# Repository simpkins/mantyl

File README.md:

# Mantyl: concave split keyboard

This repository contains the CAD design code and firmware for my custom
keyboard.

# Keyboard Model

The `cad` directory contains code for generating the keyboard model, using
Python scripts for [Blender](https://www.blender.org/).

# Firmware

The `src` directory contains the firmware for the keyboard.  I use a
[FeatherS3](https://esp32s3.com/feathers3.html) for the microcontroller,
and the firmware code is built with the
[ESP-IDF](https://github.com/espressif/esp-idf).

# Gallery

Some more images can be found in the [img](img) directory.

# Documentation

The [doc](doc) directory contains various documentation.  The
[assembly.md](doc/assembly.md) and [wiring.md](doc/wiring.md) files may be of
interest if you are looking to print and assemble your own version of the
keyboard.

# Inspiration

I've used [Maltron](https://www.maltron.com/) keyboards for quite a long time.
My original Maltron keyboard was a PS/2 model, and back in 2013 I built my own
[keyboard controller](https://github.com/simpkins/avrpp) for it using a
[Teensy++ 2.0](https://www.pjrc.com/store/teensypp.html) microcontroller, in
order to convert it to a USB keyboard.

The layout for this keyboard is heavily influenced by the Maltron layout--I
wanted it to be fairly similar since I've used the Maltron layout for so long.

For generating the keyboard model programmatically I took some inspiration from
the [Dactyl-Manuform](https://github.com/abstracthat/dactyl-manuform) keyboard.
I initially started out using OpenSCAD, but quickly found it fairly limiting
and switched to using Python APIs for blender.  For some choices of the
electronic components, particularly the SX1509, I relied on some of the
component selection from my co-worker Wez's
[Halfdeck](https://github.com/wez/halfdeck) keyboard.

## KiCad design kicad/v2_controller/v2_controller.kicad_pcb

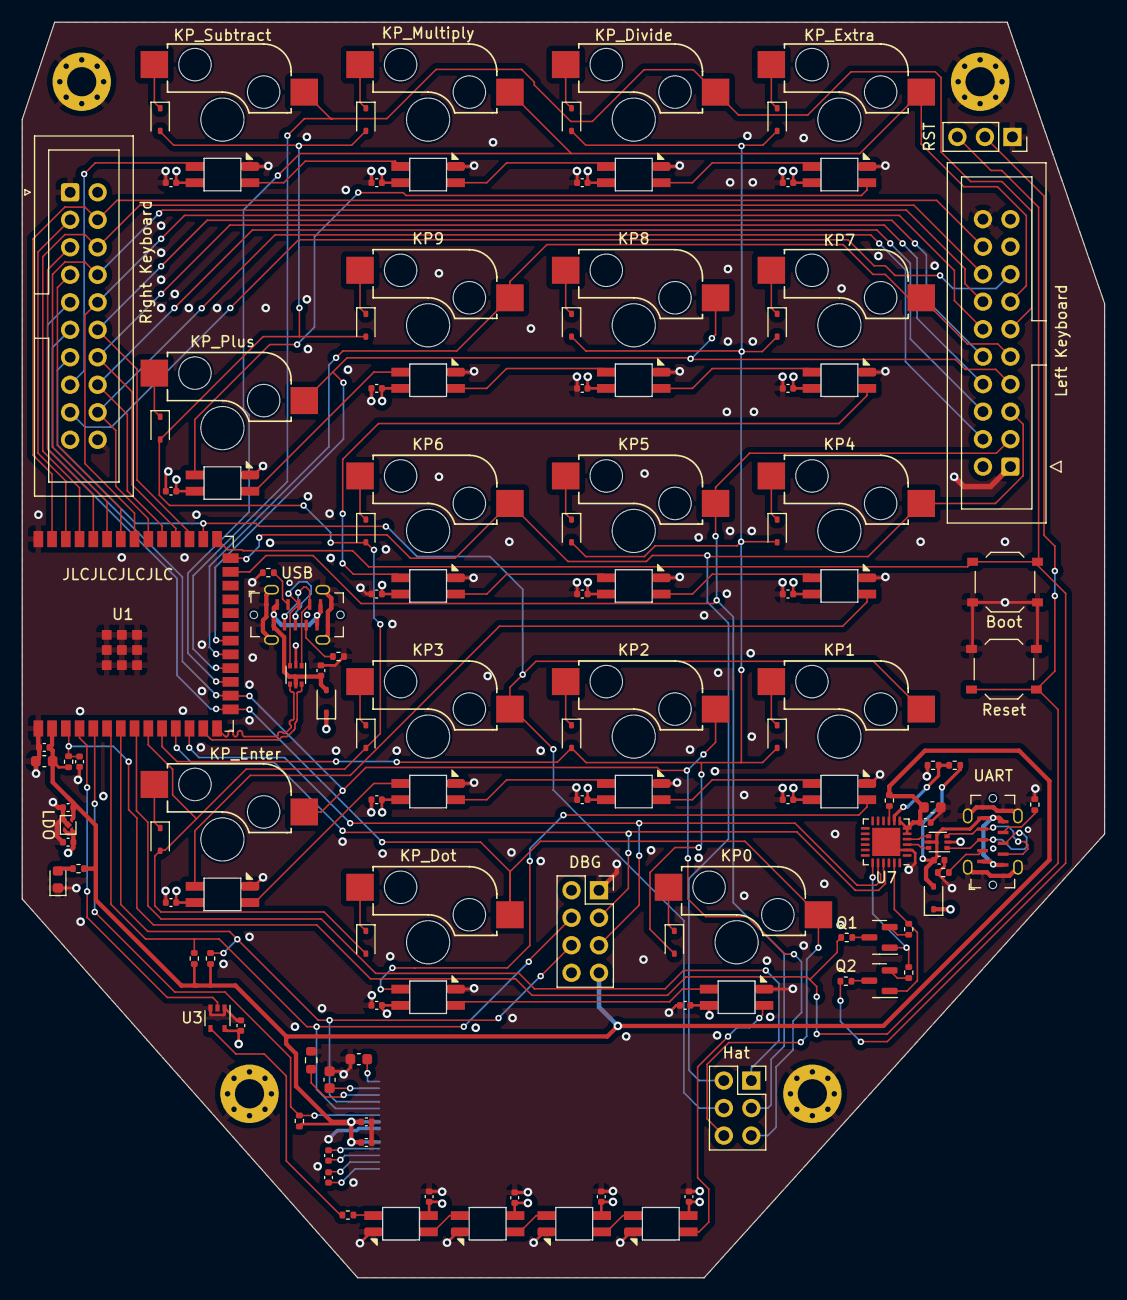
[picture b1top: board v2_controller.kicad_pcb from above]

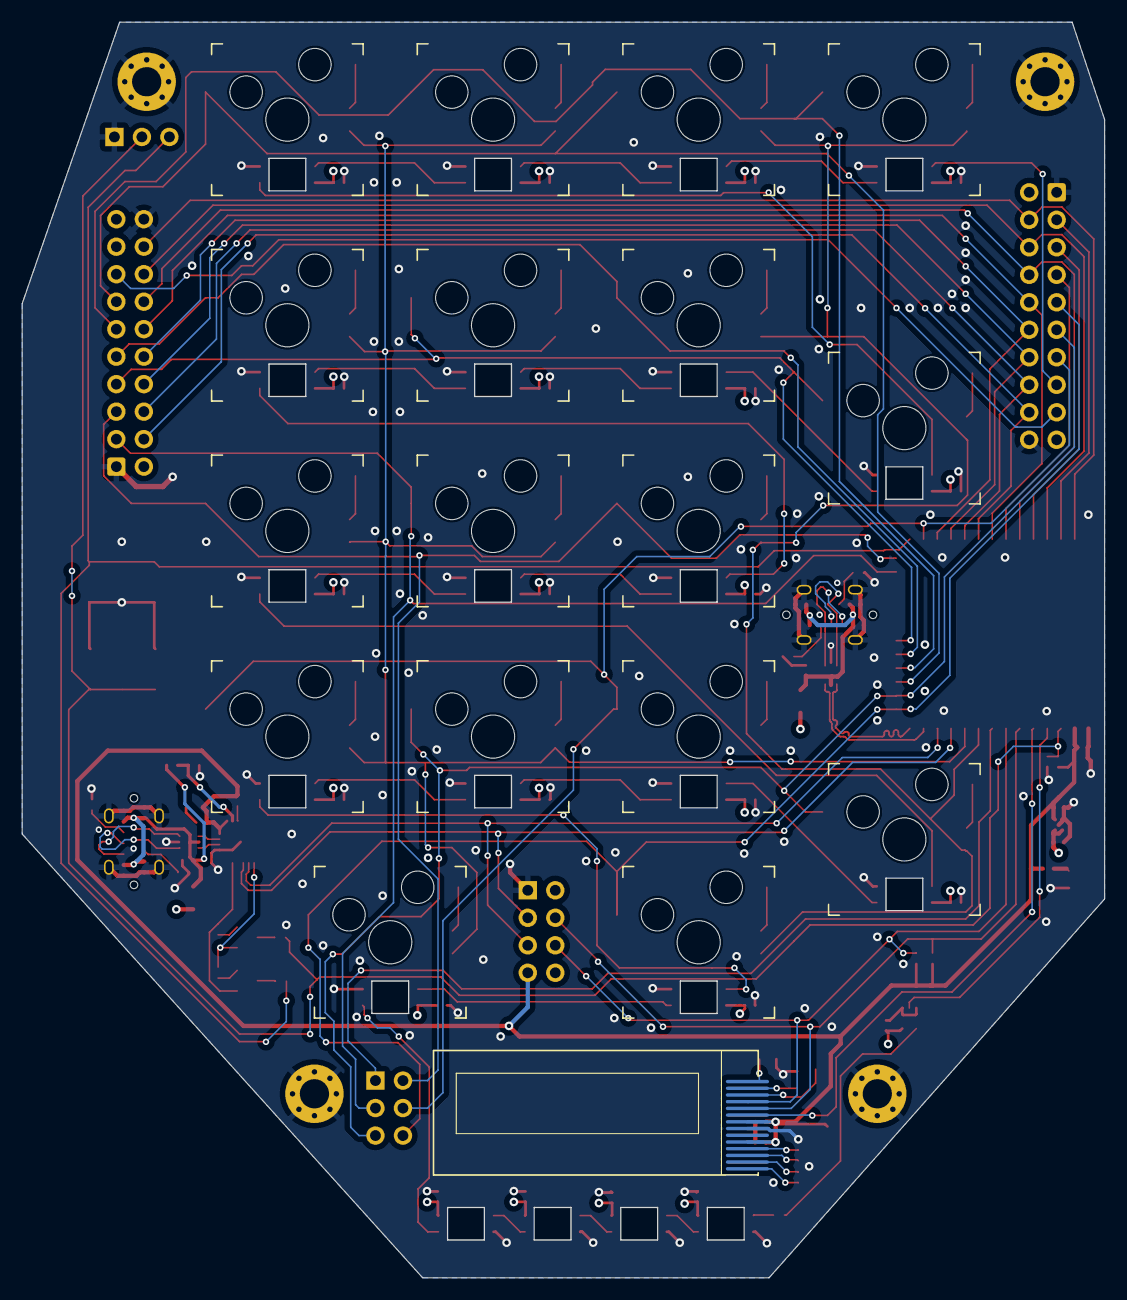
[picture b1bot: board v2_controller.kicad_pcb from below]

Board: 4 copper layers, 100.0 x 116.0 mm, 135 parts (18 on the bottom side), 105 nets.

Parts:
C1, C4, C5, C8, C9, C11, C12: 1uF; C_0402_1005Metric
C2, C6, C7, C17: 10uF; C_0603_1608Metric
C3, C10, C15, C16, C18, C19, C20, C21, C22, C23, C24, C25, C26, C27, C28, C29, C30, C31, C32, C33, C34, C35, C36, C37, C38, C39: 100nF; C_0402_1005Metric
D1, D2, D3, D4, D5, D6, D7, D8, D9, D10, D11, D12, D13, D14, D15, D16, D17, D38, D39, D40, D41: SK6812 Mini-E; SK6812-MINI-E
D18, D19: 1N5819WS; D_SOD-323
D20: Red LED; LED_0603_1608Metric
D21, D22, D23, D24, D25, D26, D27, D28, D29, D30, D31, D32, D33, D34, D35, D36, D37: 1N4148WS; D_SOD-323
H1, H2, H3, H4: MountingHole_Pad; MountingHole_2.7mm_M2.5_Pad_Via
J1, J2: USB_C_Receptacle_USB2.0; GT-USB-7090x
J3, J4: Conn_02x10_Odd_Even; IDC-Header_2x10_P2.54mm_Vertical
J5: Conn_02x04_Odd_Even; PinSocket_2x04_P2.54mm_Vertical
J6: Conn_02x03_Odd_Even; PinSocket_2x03_P2.54mm_Vertical
J7: Conn_01x03; PinSocket_1x03_P2.54mm_Vertical
Q1, Q2: S8050; SOT-23
R1, R4, R5, R17: 10k; R_0402_1005Metric
R2, R3: 4.7k; R_0402_1005Metric
R6, R7: 0; R_0402_1005Metric
R8, R9, R10, R11, R12: 5.1k; R_0402_1005Metric
R13: 22.1k; R_0402_1005Metric
R14: 47.5k; R_0402_1005Metric
R15: 1k; R_0402_1005Metric
R16: 470; R_0402_1005Metric
R18: 390k; R_0603_1608Metric
SW1: KP0; Kailh_socket_MX_platemount
SW2: KP_Dot; Kailh_socket_MX_platemount
SW3: KP1; Kailh_socket_MX_platemount
SW4: KP2; Kailh_socket_MX_platemount
SW5: KP3; Kailh_socket_MX_platemount
SW6: KP_Enter; Kailh_socket_MX_platemount
SW7: KP4; Kailh_socket_MX_platemount
SW8: KP5; Kailh_socket_MX_platemount
SW9: KP6; Kailh_socket_MX_platemount
SW10: KP7; Kailh_socket_MX_platemount
SW11: KP8; Kailh_socket_MX_platemount
SW12: KP9; Kailh_socket_MX_platemount
SW13: KP_Plus; Kailh_socket_MX_platemount
SW14: KP_Extra; Kailh_socket_MX_platemount
SW15: KP_Divide; Kailh_socket_MX_platemount
SW16: KP_Multiply; Kailh_socket_MX_platemount
SW17: KP_Subtract; Kailh_socket_MX_platemount
SW18: Boot; SW_Push_1P1T_XKB_TS-1187A
SW19: Reset; SW_Push_1P1T_XKB_TS-1187A
U1: ESP32-S3-WROOM-1-N16R8; ESP32-S3-WROOM-1
U2: SSD1306_I2C; SSD1306_OLED-0.91-128x32_Folded
U3: 74AHCT1G125; SOT-353_SC-70-5
U4: NCP167BMX330TBG; OnSemi_XDFN4-1EP_1.0x1.0mm_EP0.52x0.52mm
U5, U6: USBLC6-2P6; SOT-666
U7: CP2102N-Axx-xQFN24; QFN-24-1EP_4x4mm_P0.5mm_EP2.6x2.6mm

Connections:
+3.3V: C2.1, C3.1, C4.2, C5.2, C12.1, C17.2, C18.2, J5.7, R1.1, R2.1, R3.1, R12.2, R15.2, R17.1, U1.2 (3V3), U2.5 (VBAT), U2.8 (VDD), U4.1 (OUT), U7.5 (VIO), U7.6 (VDD), U7.7 (VREGIN)
+5V: C10.1, C11.1, C19.2, C20.2, C21.2, C22.2, C23.2, C24.2, C25.2, C26.2, C27.2, C28.2, C29.2, C30.2, C31.2, C32.2, C33.2, C34.2, C35.2, C36.2, C37.2, C38.2, C39.2, D1.1 (VDD), D2.1 (VDD), D3.1 (VDD), D4.1 (VDD), D5.1 (VDD), D6.1 (VDD), D7.1 (VDD), D8.1 (VDD), D9.1 (VDD), D10.1 (VDD), D11.1 (VDD), D12.1 (VDD), D13.1 (VDD), D14.1 (VDD), D15.1 (VDD), D16.1 (VDD), D17.1 (VDD), D18.1 (K), D19.1 (K), D38.1 (VDD), D39.1 (VDD), D40.1 (VDD), D41.1 (VDD), J3.2, J4.2, J5.2, U3.5 (VCC), U4.3 (EN), U4.4 (IN)
/ESP32/CHIP_PU: C1.1, J7.2, R1.2, R6.1, SW19.2, U1.3 (EN)
/ESP32/COL0: J3.18, J4.4, U1.39 (GPIO1)
/ESP32/COL1: J3.16, J4.6, U1.37 (GPIO43/U0TXD)
/ESP32/COL2: J3.14, J4.8, U1.35 (GPIO42)
/ESP32/COL3: J3.12, J4.10, U1.33 (GPIO40)
/ESP32/COL4: J3.10, J4.12, U1.29 (GPIO36)
/ESP32/COL5: J3.8, J4.14, U1.30 (GPIO37)
/ESP32/COL6: J3.6, J4.16, U1.31 (GPIO38)
/ESP32/COL7: J3.4, J4.18, U1.32 (GPIO39)
/ESP32/COL8: D21.2 (A), D23.2 (A), D24.2 (A), D27.2 (A), D28.2 (A), D30.2 (A), D31.2 (A), D34.2 (A), D35.2 (A), U1.10 (GPIO17/U1TXD)
/ESP32/COL9: D22.2 (A), D25.2 (A), D26.2 (A), D29.2 (A), D32.2 (A), D33.2 (A), D36.2 (A), D37.2 (A), U1.9 (GPIO16/XTAL_32K_N)
/ESP32/COL10: J6.1, U1.8 (GPIO15/XTAL_32K_P)
/ESP32/GPIO0: J7.3, R7.1, SW18.2, U1.27 (GPIO0/BOOT)
/ESP32/LED_DIN_3V3: U1.4 (GPIO4), U3.2
/ESP32/LED_LEFT_DIN: J3.15, J4.17
/ESP32/LED_NUMPAD_DIN: R16.1, U3.4
/ESP32/LED_RIGHT_DIN: D17.2 (DOUT), J4.15
/ESP32/OLED_RST: R17.2, U1.5 (GPIO5), U2.9 (RES#)
/ESP32/ROW0: J3.13, SW14.1, SW16.1, U1.17 (GPIO9)
/ESP32/ROW1: J3.11, SW15.1, SW17.1, U1.18 (GPIO10)
/ESP32/ROW2: J3.9, SW10.1, SW12.1, U1.19 (GPIO11)
/ESP32/ROW3: J3.7, SW11.1, SW13.1, U1.20 (GPIO12)
/ESP32/ROW4: J3.5, J6.2, SW7.1, SW9.1, U1.26 (GPIO45)
/ESP32/ROW5: J3.3, J6.3, SW8.1, U1.25 (GPIO48/SPICLK_N)
/ESP32/ROW6: J4.13, J6.4, SW3.1, SW5.1, U1.28 (GPIO35)
/ESP32/ROW7: J4.11, J6.5, SW4.1, SW6.1, U1.16 (GPIO46)
/ESP32/ROW8: J4.9, J6.6, SW1.1, SW2.1, U1.15 (GPIO3)
/ESP32/ROW9: J4.7, U1.34 (GPIO41)
/ESP32/ROW10: J4.5, U1.36 (GPIO44/U0RXD)
/ESP32/ROW11: J4.3, U1.38 (GPIO2)
/ESP32/SCL: J5.4, R2.2, U1.6 (GPIO6), U2.10 (SCL)
/ESP32/SDA: J5.6, R3.2, U1.7 (GPIO7), U2.11 (SDA)
/ESP32/UART_DTR: Q2.1 (E), R4.1, U7.23 (~DTR)
/ESP32/UART_RTS: Q1.1 (E), R5.1, U7.19 (~RTS)
/ESP32/UART_RX: J5.3, U1.11 (GPIO18/U1RXD), U7.21 (TXD)
/ESP32/UART_TX: J5.5, U1.12 (GPIO8), U7.20 (RXD)
/ESP32/USB_D+: U1.14 (GPIO20/USB_D+), U5.4 (I/O2)
/ESP32/USB_D-: U1.13 (GPIO19/USB_D-), U5.6 (I/O1)
/LEDs/LED_NP_MAIN_DIN: D1.4 (DIN), D41.2 (DOUT)
/USB/UART_USB_D+: U6.6 (I/O1), U7.3 (D+)
/USB/UART_USB_D-: U6.4 (I/O2), U7.4 (D-)
/USB/UART_USB_VBUS: C16.1, D19.2 (A), J2.A4 (VBUS), J2.A9 (VBUS), J2.B4 (VBUS), J2.B9 (VBUS), R13.1, U6.5 (VBUS)
/USB/USB_VBUS: C15.1, D18.2 (A), J1.A4 (VBUS), J1.A9 (VBUS), J1.B4 (VBUS), J1.B9 (VBUS), U5.5 (VBUS)
GND: C1.2, C2.2, C3.2, C4.1, C5.1, C6.2, C7.2, C10.2, C11.2, C12.2, C15.2, C16.2, C17.1, C18.1, C19.1, C20.1, C21.1, C22.1, C23.1, C24.1, C25.1, C26.1, C27.1, C28.1, C29.1, C30.1, C31.1, C32.1, C33.1, C34.1, C35.1, C36.1, C37.1, C38.1, C39.1, D1.3 (VSS), D2.3 (VSS), D3.3 (VSS), D4.3 (VSS), D5.3 (VSS), D6.3 (VSS), D7.3 (VSS), D8.3 (VSS), D9.3 (VSS), D10.3 (VSS), D11.3 (VSS), D12.3 (VSS), D13.3 (VSS), D14.3 (VSS), D15.3 (VSS), D16.3 (VSS), D17.3 (VSS), D20.1 (K), D38.3 (VSS), D39.3 (VSS), D40.3 (VSS), D41.3 (VSS), H1.1, H2.1, H3.1, H4.1, J1.A1 (GND), J1.A12 (GND), J1.B1 (GND), J1.B12 (GND), J1.S1 (SHIELD), J2.A1 (GND), J2.A12 (GND), J2.B1 (GND), J2.B12 (GND), J2.S1 (SHIELD), J3.1, J3.20, J4.1, J4.20, J5.1, J7.1, R8.2, R9.2, R10.2, R11.2, R14.2, R18.2, SW18.1, SW19.1, U1.1 (GND), U1.40 (GND), U1.41 (GND), U2.7 (VSS), U3.1, U3.3 (GND), U4.2 (GND), U4.5 (EPAD), U5.2 (GND), U6.2 (GND), U7.2 (GND), U7.25 (GND)
unnamed: D1.2 (DOUT), D2.4 (DIN)
unnamed: D2.2 (DOUT), D3.4 (DIN)
unnamed: D3.2 (DOUT), D4.4 (DIN)
unnamed: D4.2 (DOUT), D5.4 (DIN)
unnamed: D5.2 (DOUT), D6.4 (DIN)
unnamed: D6.2 (DOUT), D7.4 (DIN)
unnamed: D7.2 (DOUT), D8.4 (DIN)
unnamed: D8.2 (DOUT), D9.4 (DIN)
unnamed: D9.2 (DOUT), D10.4 (DIN)
unnamed: D10.2 (DOUT), D11.4 (DIN)
unnamed: D11.2 (DOUT), D12.4 (DIN)
unnamed: D12.2 (DOUT), D13.4 (DIN)
unnamed: D13.2 (DOUT), D14.4 (DIN)
unnamed: D14.2 (DOUT), D15.4 (DIN)
unnamed: D15.2 (DOUT), D16.4 (DIN)
unnamed: D16.2 (DOUT), D17.4 (DIN)
unnamed: D20.2 (A), R12.1
unnamed: D21.1 (K), SW1.2
unnamed: D22.1 (K), SW2.2
unnamed: D23.1 (K), SW3.2
unnamed: D24.1 (K), SW4.2
unnamed: D25.1 (K), SW5.2
unnamed: D26.1 (K), SW6.2
unnamed: D27.1 (K), SW7.2
unnamed: D28.1 (K), SW8.2
unnamed: D29.1 (K), SW9.2
unnamed: D30.1 (K), SW10.2
unnamed: D31.1 (K), SW11.2
unnamed: D32.1 (K), SW12.2
unnamed: D33.1 (K), SW13.2
unnamed: D34.1 (K), SW14.2
unnamed: D35.1 (K), SW15.2
unnamed: D36.1 (K), SW16.2
unnamed: D37.1 (K), SW17.2
unnamed: D38.4 (DIN), R16.2
unnamed: D38.2 (DOUT), D39.4 (DIN)
unnamed: D39.2 (DOUT), D40.4 (DIN)
unnamed: D40.2 (DOUT), D41.4 (DIN)
unnamed: J1.A5 (CC1), R8.1
unnamed: J1.B5 (CC2), R9.1
unnamed: J1.A6 (D+), J1.B6 (D+), U5.3 (I/O2)
unnamed: J1.A7 (D-), J1.B7 (D-), U5.1 (I/O1)
unnamed: J2.A5 (CC1), R10.1
unnamed: J2.B5 (CC2), R11.1
unnamed: J2.A6 (D+), J2.B6 (D+), U6.1 (I/O1)
unnamed: J2.A7 (D-), J2.B7 (D-), U6.3 (I/O2)
unnamed: Q1.2 (B), R4.2
unnamed: Q1.3 (C), R6.2
unnamed: Q2.2 (B), R5.2
unnamed: Q2.3 (C), R7.2
unnamed: C8.1, U2.4 (C1N)
unnamed: C8.2, U2.3 (C1P)
unnamed: C9.1, U2.2 (C2N)
unnamed: C9.2, U2.1 (C2P)
unnamed: R18.1, U2.12 (IREF)
unnamed: C6.1, U2.14 (VCC)
unnamed: C7.1, U2.13 (VCOMH)
unnamed: R13.2, R14.1, U7.8 (VBUS)
unnamed: R15.1, U7.9 (~RST)

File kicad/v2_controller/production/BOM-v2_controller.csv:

"Comment","Designator","Footprint","LCSC"
"1k","R15","R0402","C11702"
"74AHCT1G125","U3","SOT-353_SC-70-5","C151417"
"0","R6,R7","R0402","C17168"
"1N5819WS","D18,D19","SOD-323","C191023"
"1N4148WS","D21,D22,D23,D24,D25,D26,D27,D28,D29,D30,D31,D32,D33,D34,D35,D36,D37","SOD-323","C2128"
"S8050","Q1,Q2","SOT-23","C2150"
"Red LED","D20","LED0603","C2286"
"390k","R18","R0603","C23150"
"470","R16","R0402","C25117"
"10k","R1,R17,R4,R5","R0402","C25744"
"22.1k","R13","R0402","C25768"
"47.5k","R14","R0402","C25792"
"4.7k","R2,R3","R0402","C25900"
"5.1k","R10,R11,R12,R8,R9","R0402","C25905"
"USBLC6-2P6","U5,U6","SOT-666","C2827693"
"Conn_02x03_Odd_Even","J6","PinSocket_2x03_P2.54mm_Vertical","C2829893"
"ESP32-S3-WROOM-1-N16R8","U1","ESP32-S3-WROOM-1","C2913202"
"USB_C_Receptacle_USB2.0","J1,J2","GT-USB-7090x","C3019715"
"100nF","C10,C15,C16,C18,C19,C20,C21,C22,C23,C24,C25,C26,C27,C28,C29,C3,C30,C31,C32,C33,C34,C35,C36,C37,C38,C39","C0402","C307331"
"Boot","SW18,SW19","SW_Push_1P1T_XKB_TS-1187A","C318884"
"Conn_02x10_Odd_Even","J3,J4","IDC-Header_2x10_P2.54mm_Vertical","C3405"
"SK6812 Mini-E","D1,D10,D11,D12,D13,D14,D15,D16,D17,D2,D3,D38,D39,D4,D40,D41,D5,D6,D7,D8,D9","SK6812-MINI-E","C5149201"
"KP0","SW1,SW10,SW11,SW12,SW13,SW14,SW15,SW16,SW17,SW2,SW3,SW4,SW5,SW6,SW7,SW8,SW9","Kailh_socket_MX_platemount","C5156480"
"1uF","C1,C11,C12,C4,C5,C8,C9","C0402","C52923"
"NCP167BMX330TBG","U4","OnSemi_XDFN4-1EP_1.0x1.0mm_EP0.52x0.52mm","C892227"
"10uF","C17,C2,C6,C7","C0603","C96446"
"CP2102N-Axx-xQFN24","U7","QFN-24-1EP_4x4mm_P0.5mm_EP2.6x2.6mm","C969151"

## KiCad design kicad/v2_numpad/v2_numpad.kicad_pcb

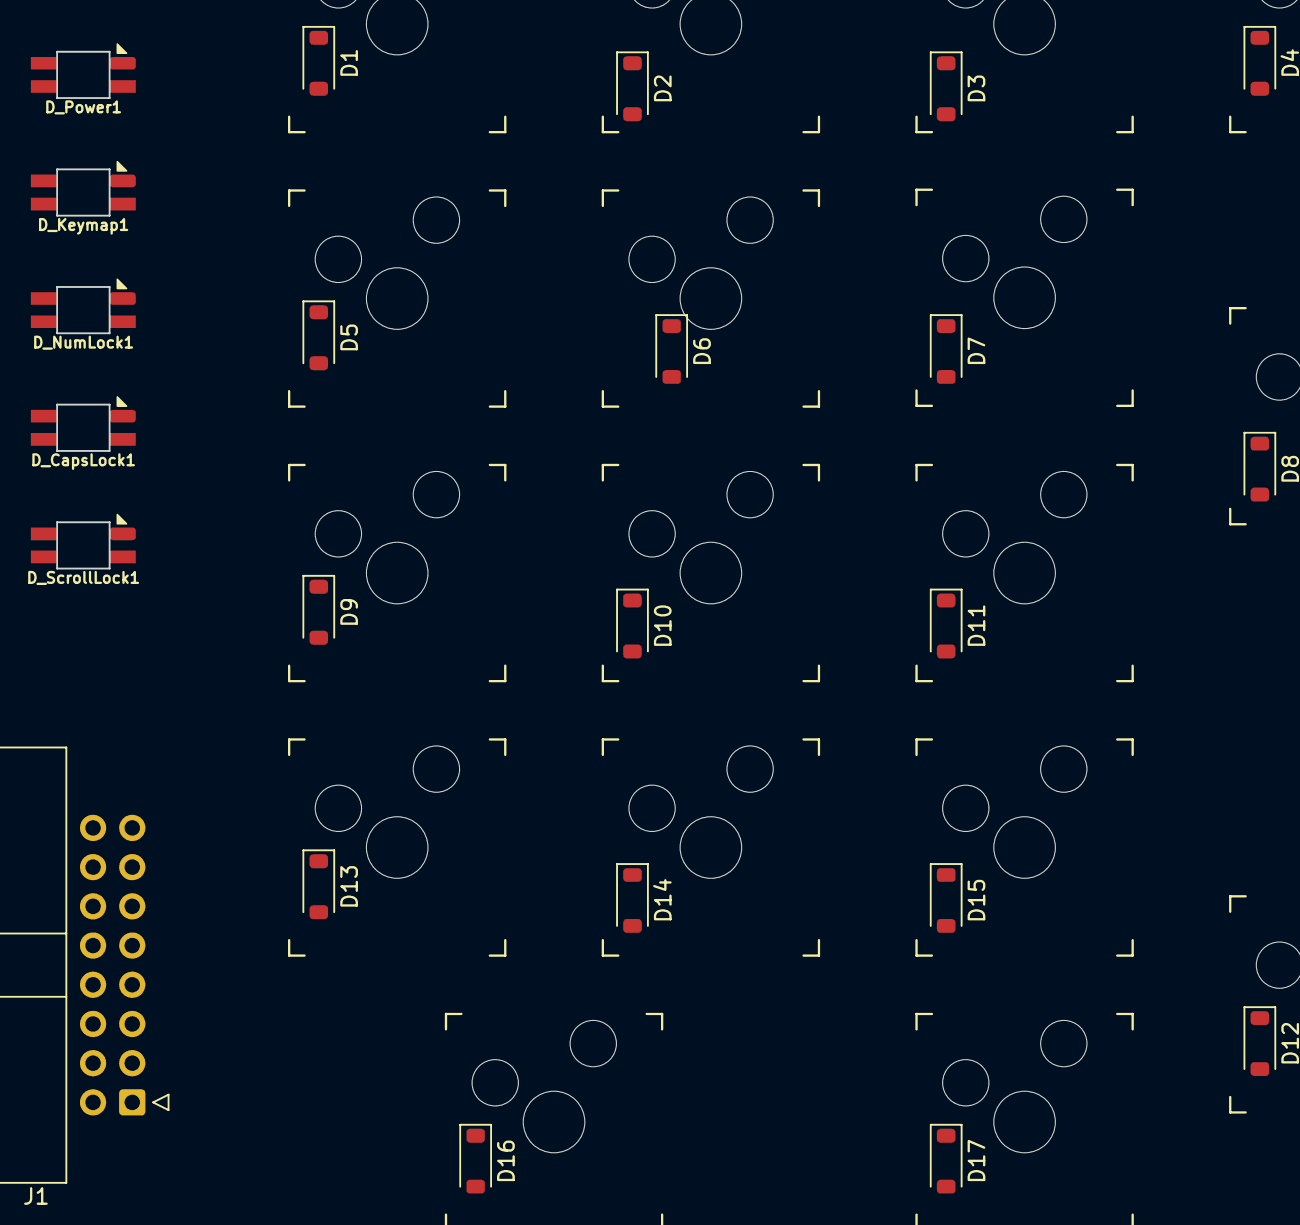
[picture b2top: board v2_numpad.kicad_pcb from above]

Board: 2 copper layers, 40 parts (0 on the bottom side), 35 nets, no tracks yet.

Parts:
D1, D2, D3, D4, D5, D6, D7, D8, D9, D10, D11, D12, D13, D14, D15, D16, D17: 1N4148W; D_SOD-123
D_CapsLock1: SK6812 Mini-E; SK6812-MINI-E
D_Keymap1: SK6812 Mini-E; SK6812-MINI-E
D_NumLock1: SK6812 Mini-E; SK6812-MINI-E
D_Power1: SK6812 Mini-E; SK6812-MINI-E
D_ScrollLock1: SK6812 Mini-E; SK6812-MINI-E
J1: Conn_02x08_Top_Bottom; IDC-Header_2x08_P2.54mm_Horizontal
SW_Dot1: Kailh_socket_MX_platemount
SW_Enter1: Kailh_socket_MX_platemount
SW_Extra1: Kailh_socket_MX_platemount
SW_Minus1: Kailh_socket_MX_platemount
SW_NP0, SW_NP1, SW_NP2, SW_NP3, SW_NP4, SW_NP5, SW_NP6, SW_NP7, SW_NP8, SW_NP9: Kailh_socket_MX_platemount
SW_Plus1: Kailh_socket_MX_platemount
SW_Slash1: Kailh_socket_MX_platemount
SW_Star1: Kailh_socket_MX_platemount

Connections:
+5V: D_CapsLock1.1 (VDD), D_Keymap1.1 (VDD), D_NumLock1.1 (VDD), D_Power1.1 (VDD), D_ScrollLock1.1 (VDD), J1.9
/C8: D1.2 (A), D2.2 (A), D5.2 (A), D6.2 (A), D9.2 (A), D10.2 (A), D13.2 (A), D14.2 (A), D16.2 (A), J1.15
/C9: D3.2 (A), D4.2 (A), D7.2 (A), D8.2 (A), D11.2 (A), D12.2 (A), D15.2 (A), D17.2 (A), J1.16
/LED_Data: D_ScrollLock1.4 (DIN), J1.12
/R0: J1.2, SW_Dot1.2, SW_NP0.2
/R1: J1.3, SW_NP1.2, SW_NP3.2
/R2: J1.4, SW_Enter1.2, SW_NP2.2
/R3: J1.5, SW_NP4.2, SW_NP6.2
/R4: J1.6, SW_NP5.2
/R5: J1.7, SW_NP7.2, SW_NP9.2
/R6: J1.8, SW_NP8.2, SW_Plus1.2
/R7: J1.10, SW_Extra1.2, SW_Star1.2
/R8: J1.11, SW_Minus1.2, SW_Slash1.2
GND: D_CapsLock1.3 (VSS), D_Keymap1.3 (VSS), D_NumLock1.3 (VSS), D_Power1.3 (VSS), D_ScrollLock1.3 (VSS), J1.1
unnamed: D1.1 (K), SW_Extra1.1
unnamed: D2.1 (K), SW_Slash1.1
unnamed: D3.1 (K), SW_Star1.1
unnamed: D4.1 (K), SW_Minus1.1
unnamed: D5.1 (K), SW_NP7.1
unnamed: D6.1 (K), SW_NP8.1
unnamed: D7.1 (K), SW_NP9.1
unnamed: D8.1 (K), SW_Plus1.1
unnamed: D9.1 (K), SW_NP4.1
unnamed: D10.1 (K), SW_NP5.1
unnamed: D11.1 (K), SW_NP6.1
unnamed: D12.1 (K), SW_Enter1.1
unnamed: D13.1 (K), SW_NP1.1
unnamed: D14.1 (K), SW_NP2.1
unnamed: D15.1 (K), SW_NP3.1
unnamed: D16.1 (K), SW_NP0.1
unnamed: D17.1 (K), SW_Dot1.1
unnamed: D_CapsLock1.4 (DIN), D_ScrollLock1.2 (DOUT)
unnamed: D_CapsLock1.2 (DOUT), D_NumLock1.4 (DIN)
unnamed: D_Keymap1.4 (DIN), D_NumLock1.2 (DOUT)
unnamed: D_Keymap1.2 (DOUT), D_Power1.4 (DIN)

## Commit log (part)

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2022-06-05 Begin adding logic for SX1509 keypad
2022-06-11 [cad] improve blender translation and rotation utilities
2022-06-11 [cad] start working on a holder for the switch sockets
2022-06-14 [cad] begin working on a detached grid for socket holders
2022-06-17 [cad] work on socket holder grid
    This isn't quite working yet; the blender unions aren't quite doing
    what I want. I may need to update the generation logic to avoid unions,
    and manually construct more of the mesh.
2022-06-19 [cad] more work on manual socket holder mesh
2022-06-19 [cad] clean up the socket holder base plate
    This avoids some slightly weird geometry that blender produces
    otherwise.
2022-06-19 [cad] increase wall thickness around diode holder
2022-06-19 [cad] complete the socket holder grid
2022-06-21 [cad] truncate socket holders for top key row
    Remove the diode holder and wire holder on the socket holders that
    are upside down on the top row.
2022-06-26 [cad] split the main.py file into separate files for each component
2022-06-28 [cad] simplify the key socket wire holders
    The features on the previous wire holders were too small to print well.
2022-06-28 [cad] provide a little more clearance for the underlay
    Adjust some of the keyboard walls to make more room for the switch legs
    and underlay. This allows the underlay to all be facing one direction,
    rather than having to place some key switches upside down near the
    walls.
2022-06-29 [cad] fix a big in auto_update.py if some modules were never imported
    Don't throw an exception if some of the watched modules were never
    imported in the first place.
2022-06-29 [cad] add the left underlays
2022-06-30 [cad] minor cleanup, and create test print for I2C connector holder
2022-07-01 [cad] add a file to generate all parts for the right half
2022-07-02 [cad] adjust wrist rest screw hole spacing
2022-07-03 [src] add a note about enabling C++17 support for Arduino
2022-07-06 [cad] rename export_all.py to generate_stl.py
2022-07-09 [cad] rework the OLED display cutout
2022-07-10 [cad] more tweaks to OLED cutout, plus add a backplate
2022-07-10 [cad] shrink the screw hole size on the OLED backplate
2022-07-10 [cad] some more OLED backplate tweaks
2022-07-12 [cad] work on the USB cutout
2022-07-14 [cad] add a backplate for the USB connector
2022-07-16 [cad] change the SX1509 holder to use screw stand-offs
2022-07-16 [cad] additional minor tweaks to the left keyboard
2022-07-17 Remove older unused image file
2022-07-17 [firmware] initial basic project using the ESP-IDF directly
2022-07-19 [firmware] start adding SX1509 component
2022-07-23 [doc] add some docs about the key switch matrix wiring
    Also move the assembly notes into the doc folder
2022-07-23 [doc] additional updates to wiring notes
2022-07-26 [firmware] check in sdkconfig updates from newer ESP-IDF version
2022-07-28 [firmware] implement lower case letters for the font
2022-07-31 [firmware] some more font glyphs
2022-07-31 [firmware] add some utility functions for displaying text
2022-08-04 [firmware] some keypad scanning debug code
2022-08-09 [firmware] more minor tweaks for keypad testing
2022-08-12 [firmware] implement keypad scanning with proper time handling
2022-08-13 [doc] rename some docs files for consistency
2022-08-14 [firmware] use a separate I2C bus for the right half
    This should the likelihood of any issues with the connection to the
    right half causing problems for the i2c devices in the left half.
    This also makes it easier to independently reset the two halves.
    This may also make it easier to detect the right half being connected or
    disconnected if I put the pull-up resistors for the right I2C bus inside
    the right half of the keyboard. I should be able to detect the right
2022-08-17 [firmware] update pin config to match finalized settings
2022-08-19 [firmware] fix right half i2c configuration
2022-08-24 [firmware] some hacky USB initialization for testing
2022-08-25 [firmware] custom USB descriptors
2022-08-27 [firmware] begin attempting to use upstream tinyusb
2022-08-27 [firmware] write log messages to the oled display
2022-08-27 [firmware] minor tweaks to initialization log messages
2022-08-27 [firmware] enable oled display fade for log messages
2022-08-27 [firmware] remove the upstream tinyusb submodule
2022-08-27 [doc] add some notes about concurrency in the firmware
2022-08-30 [firmware] add a todo comment about handling HID report errors
2022-08-30 [firmware] start wiring up handling of UI directional switch presses
2022-08-30 [firmware] correctly handle HID report send failures
2022-09-02 [cad] more work on a wrist rest
2022-09-02 [cad, update generate_stl to emit the wrist rest meshes
2022-09-03 [firmware] begin updating keymaps to support special actions
2022-09-03 [firmware] implement clear to end of line in SSD1306::write_text()
2022-09-04 [firmware] switch to using prototype USB vendor ID 6666
2022-09-05 [cad] work on the i2c cable cap
2022-09-06 [doc] update the list of sites selling DSA keycaps
2022-09-11 [firmware] re-organize the source directory layout
2022-09-13 [firmware] drop the timeout between keypad reconnect checks
    This is somewhat of a hack until we implement a proper check to detect
    when the right half SDA and SCL lines are pulled back up.
2022-09-16 [firmware] enable saving build timestamp
    Also re-enable basic VFS support.
2022-09-17 [firmware] add some contents to the status page
2022-09-18 [cad] slightly raise the E/I key
2022-09-18 Add some photos of my v1 keyboard
2022-09-20 [firmware] add a basic component for a neopixel LEDs
2022-10-23 [firmware] start working on a custom USB device implementation
    This is some new code for directly implementing a USB device stack,
    without using TinyUSB. TinyUSB's synchronization model does not really
    seem correct on FreeRTOS. For proper synchronization it seems all
    interaction with the USB state should be done from the task running
    tud_task(). The current TinyUSB behavior does not really make it easy
    to run other custom logic on this task. While I could try getting this
2022-10-23 [firmware] add a device argument to the Esp32UsbDevice constructor
    This probably doesn't really matter since the esp32s2 and esp32s3 chips
    only support a single USB device. It seems like we might as well allow
    specifying this as a parameter though, on the off chance that there is a
    chip in the future with multiple USB devices.
    Also make the constructor constexpr.
2022-10-25 [firmware] move the main code for my v1 hardware to a v1 subdirectory
2022-10-29 [firmware] add a small script to build all projects
    This makes it easier to ensure all projects build successfully.
2022-10-30 [firmware] change USB log messages to normal logs
    All work in UsbDevice is done from a normal task, not an interrupt
    context, so we don't need to use the ESP_EARLY* log macros.
2022-11-02 [firmware] more logic for compile-time descriptor creation
2022-11-13 [firmware] add a readline() utility function
2022-11-14 [usb] additional improvements to descriptor creation logic
2022-11-19 [usb] implement code to update the serial descriptor
2022-11-20 [usb] add code for handling the HID SetIdle request
2022-11-26 [usb] additional minor clean-up to the control transfer code
2022-11-28 [usb] more code for testing HID initialization
2023-04-08 [cad] update testing files to start working on a middle keypad
2023-06-13 Add pyre configuration for Python type checking
2023-06-13 [cad] continue fixing more typing errors
2023-06-13 [cad] fix all remaining typing errors in non-strict pyre mode
2023-06-13 [cad] address remaining pyre-strict errors
2023-08-02 [cad] update Mesh.transform() to transform even unused points
    Also add some utility functions for mirror transforms.
2023-08-03 [cad] add full numpad walls
2023-08-03 [cad] fix typing errors
2023-08-03 [cad] fix some edges in the numpad mesh
2023-08-04 [cad] minor numpad test display tweaks
2023-08-04 [cad] more minor code cleanup to the numpad
2023-08-04 [cad] move full test function to testing.py
2023-08-04 [cad] add bezier curve support
2023-08-05 [cad] tweak wrist rest pad holder after first test print
2023-08-05 [cad] start working on applying the wrist pad holder
2023-08-06 [cad] add feet and screw holes to the new wrist rests
2023-08-08 [cad] move my blender CAD utilities to a separate repository
    I want to use these in other projects as well, so move them to a
    separate repository, and include them here as a submodule.
2023-08-08 [cad] fix a minor issue in kbd_halves.py
2023-08-11 [kicad] rename and update numpad kicad project
2023-08-11 [kicad] start working on kicad project for v2 controller board
2023-08-11 [kicad] update schematic for v2 controller
2023-08-13 [cad] more minor testing changes for a central numpad board
2023-08-13 [cad] slightly tweak the position of the F/J keys
2023-08-13 [cad] add a bit more X separation between the keyboard halves
2023-08-14 [cad] change the numpad plate to be flat with the front corners
    Put the plate exactly in line with the front corners, so it is flat all
    the way to the front.
    I think this looks a bit less interesting, but it will make it easier
    to put a LEDs and optionally a small OLED display below the numberpad.
    Having this be flat with the numpad will make it possible to put this
    all on a single PCB with the numpad keys.
2023-08-15 [kicad] add template for ESP32-S3 boards
    Includes CP2102N, 3.3V regulator, USB connectors, power LED, and
    boot/reset switches.
2023-08-15 [kicad] update annotations in esp32s3 template
2023-08-16 [kicad] additional work on v2 controller
2023-08-16 [cad] test dimensions of numpad pcb
2023-08-17 [cad] add feet to the numpad section
2023-08-17 [cad] fix up the front left inside corner of the wrist rest
    This cleans up the mesh and flattens the inside walls near the screw
    holes.
2023-08-17 [kicad] add a debug header to the v2 controller
2023-08-17 [kicad] renumber key diodes, and clean up column wiring
2023-08-17 [kicad] more v2 controller work
    Update the switch symbols to single pole, since the XKB TS-1187A
    footprint only uses 2 pins, even though it has 4 pads.
    Also tweak the positioning of the ESP32-S3-WROOM and the board edge,
    so that the antenna is off the board.
2023-08-18 [kicad] hide most capacitor and diode labels on the silkscreen
2023-08-18 Update gitignore to exclude the kicad component layout plugin log
2023-08-18 [cad] eliminate the y shift amount from the numpad plate
    Update the original points to already take this into account,
    rather than needing to translate them afterwards.
2023-08-18 [kicad] more minor tweaks
2023-08-19 [kicad] a little more trace routing
2023-08-19 [cad] write some code to help verify PCB layout locations
2023-08-20 [cad] update the numpad PCB model with positions of major components
2023-08-22 [kicad] add ground and power planes, and finish connections
2023-08-27 [kicad] clean up additional PCB issues
2023-08-28 Clean up todo list
2023-08-28 [cad] some more modeling of the v2 controller for testing
2023-08-29 [kicad] switch OLED to mount on the back, folding the FPC connector
2023-08-30 [kicad] add a header for an external reset button
2023-08-30 [kicad] some additional detail tweaks
    - Mark the OLED as not populated (I will manually attach this on the
    bottom of the board).
    - Clean up the F.Fab layer
    - Add teardrops
2023-08-31 [cad] update OLED location to match updated Kicad PCB placement
2023-08-31 Update todo with JLCPCB component alignment issues
2023-08-31 Update JLCPCB production files
2023-08-31 [kicad] update USB connector symbols to have 14 pins
    The USB connectors I am using have 14 pins rather than 16, so update
    the symbol in the schematic to also have 14 pins. This prevents Kicad
    from complaining about these 2 extra pins when updating the PCB from the
    schematic, even though they are not connected in the schematic.
2023-09-01 [kicad] fix Kailh socket footprint to use F_Cu as the primary layer
    Kicad assumes all footprints are on the top side. The Kailh footprint
    was previously using the bottom side as its primary side, which caused
    the position export to generate the wrong side.
2023-09-01 [kicad] more updates to JLCPCB export script
2023-09-05 [cad] improve the keyboard feet
    Avoid having acute internal angles between the foot pads and the wall.
    This looks nicer and will make it easier to have an cover plate for the
    bottom.
2023-09-05 [cad] some work on producing a bottom cover
2023-09-05 [cad] work on clips and stops for the bottom cover
2023-09-06 [cad] get the cover clip test ready to print
2023-09-07 [cad] fix typing errors in foot.py
2023-09-07 [cad] some additional tweaks to the cover and clips after a test print
